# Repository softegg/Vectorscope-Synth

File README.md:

# Music Synthesizer for the Hackaday Supercon 2024/ Europe 2024 Vectorscope Badge

This is an add on for the Hackaday Superconference 2023 / Hackaday Europe(Berlin) 2024 Vectorscope badge that adds a small virtual analog synthesizer based on the [Stylish Trucker Belt Synthesizer](https://github.com/softegg/Stylish-Trucker-Belt-Synthesizer).

It should work with all of the source code from that, so for now get it there.
This has not yet been tested, so if you want to build one, be aware that it might be broken. In particular, I'm worried that the two batteries in the badge might not have the oomph to drive the vectorscope with the RPI 2040 and screen as well as the synth's Bluepill STM32, LED ring, and amplifier.

This might need additional battery or USB power support.

The design is very much in flux as we have very limited time before the show, and the modules used in the end product are going to be limited by what we can get delivered quickly in Berlin, as two week+ lead times for AliExpress parts are just not doable!
This is intended for a workshop, but we've been reluctant to commit before we are sure that it will work and that we can get the parts.

So, you might be able to do a $20 workshop and get one, or you might have to go find parts and build your own. It might work, or it might be crap.

There is so much we don't know.

I hope you can enjoy it, at least!!

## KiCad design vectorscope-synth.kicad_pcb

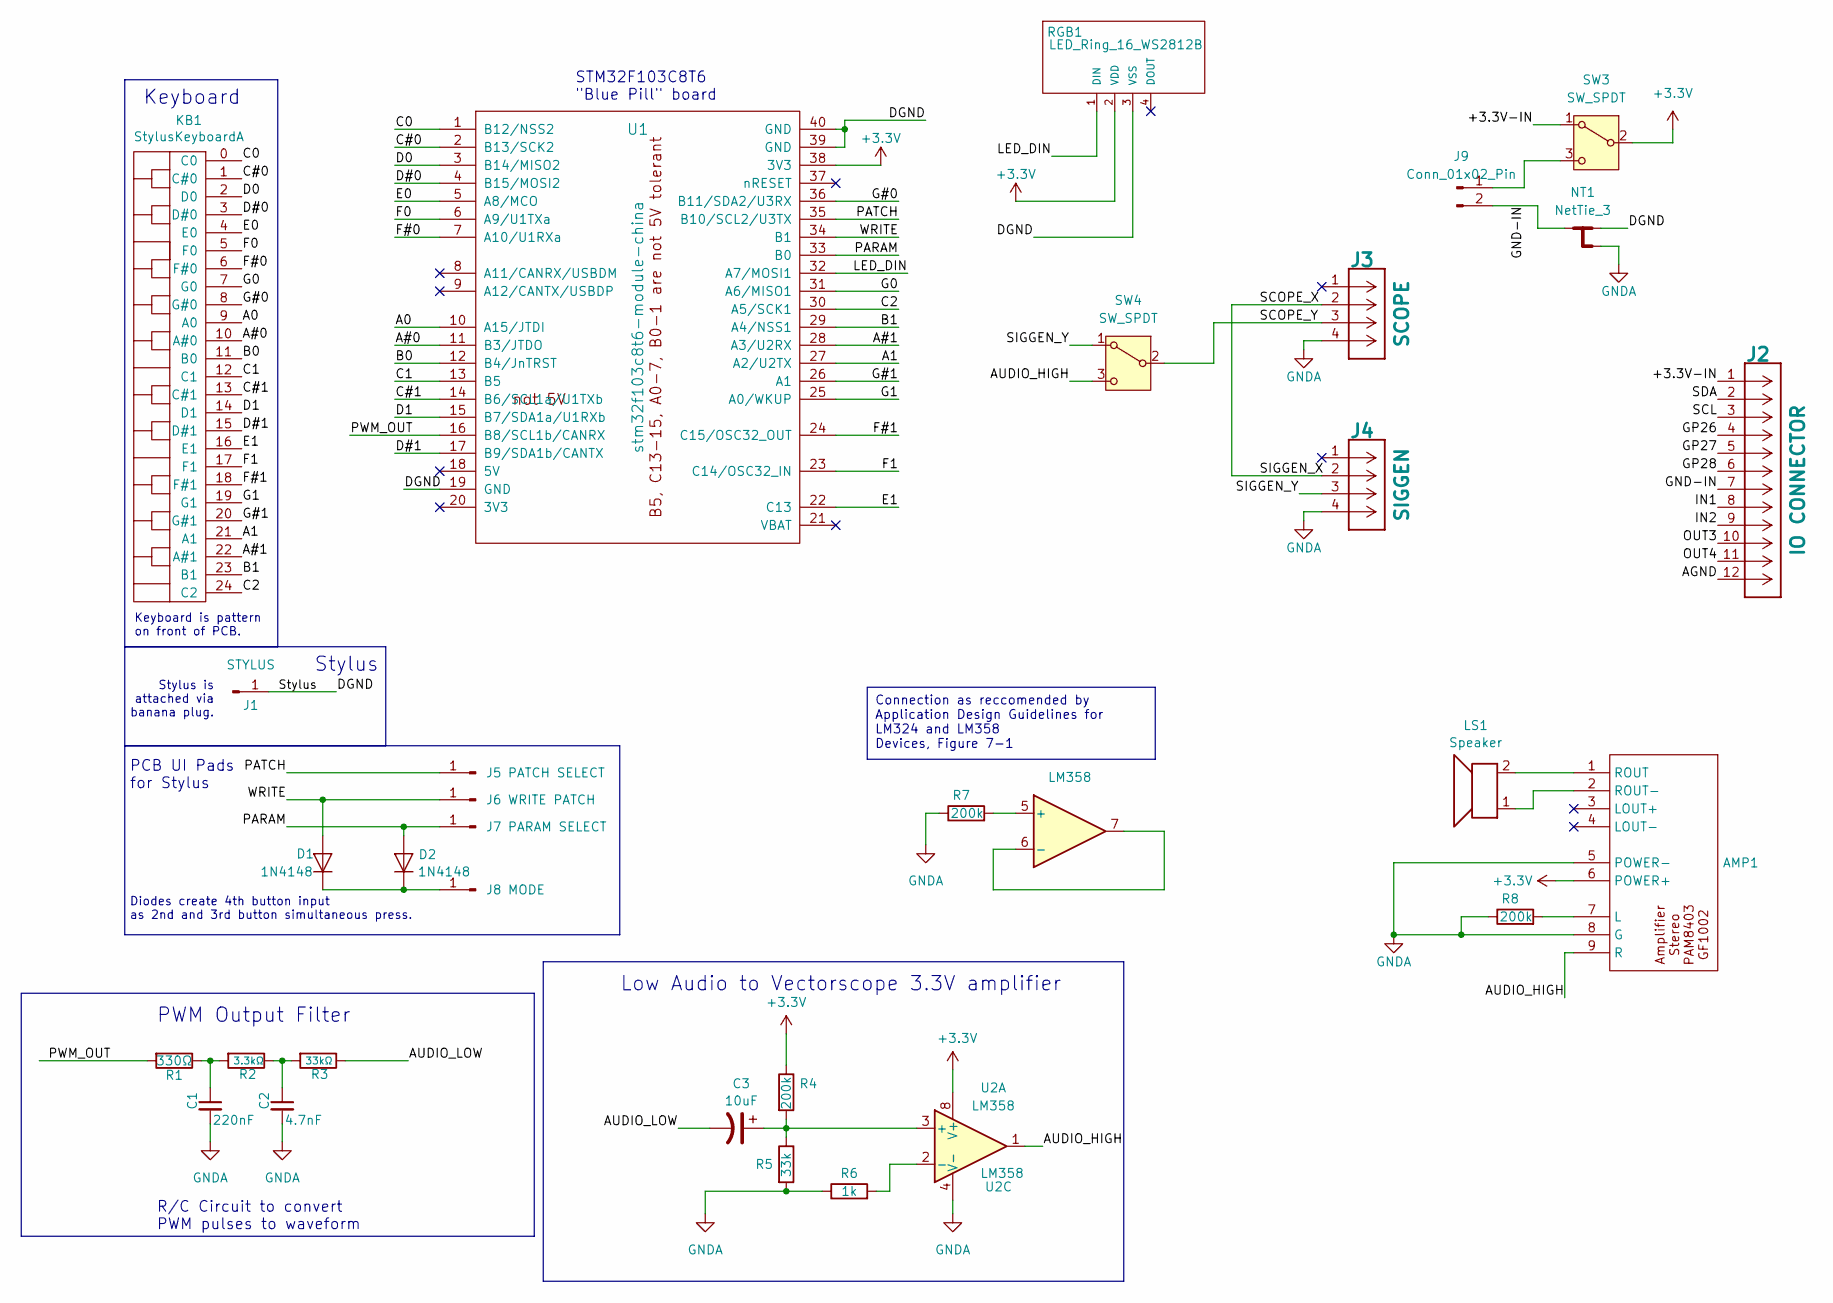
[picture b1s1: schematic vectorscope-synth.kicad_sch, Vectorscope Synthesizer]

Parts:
AMP1: GF1002-PAM8403_Amplifier_Module
C1: 220nF; C_Disc_D5.0mm_W2.5mm_P5.00mm+SMD
C2: 4.7nF; C_Disc_D5.0mm_W2.5mm_P5.00mm+SMD
C3: 10uF; CP_Radial_D5.0mm_P2.50mm
D1, D2: 1N4148; D_DO-35_SOD27_P7.62mm_Horizontal+SMD
J1: STYLUS; SmallRoundTouchPad
J2: IO CONNECTOR; PinSocket_1x12_P2.54mm_Horizontal
J3: SCOPE; PinSocket_1x04_P2.54mm_Horizontal
J4: SIGGEN; PinSocket_1x04_P2.54mm_Horizontal
J5: PATCH SELECT; SmallRoundTouchPad
J6: WRITE PATCH; SmallRoundTouchPad
J7: PARAM SELECT; SmallRoundTouchPad
J8: MODE; SmallRoundTouchPad
J9: Conn_01x02_Pin; PinHeader_1x02_P2.54mm_Vertical
KB1: StylusKeyboardA; StylusKeyboard
LS1: Speaker; PinSocket_1x02_P2.54mm_Vertical
NT1: NetTie_3; NetTie-3_SMD_Pad0.5mm
R1: 330Ω; R_Axial_DIN0204_L3.6mm_D1.6mm_P3.81mm_Horizontal+SMD804
R2: 3.3kΩ; R_Axial_DIN0204_L3.6mm_D1.6mm_P3.81mm_Horizontal+SMD804
R3: 33kΩ; R_Axial_DIN0204_L3.6mm_D1.6mm_P3.81mm_Horizontal+SMD804
R4: 200k; R_Axial_DIN0204_L3.6mm_D1.6mm_P5mm_Horizontal+SMD804
R5: 33k; R_Axial_DIN0204_L3.6mm_D1.6mm_P5mm_Horizontal+SMD804
R6: 1k; R_Axial_DIN0204_L3.6mm_D1.6mm_P5mm_Horizontal+SMD804
R7, R8: 200k; R_Axial_DIN0204_L3.6mm_D1.6mm_P7.62mm_Horizontal+SMD804
RGB1: LED_Ring_16_WS2812B; LED RING 16 WS2812B
SW3, SW4: SW_SPDT; PinHeader_1x03_P2.54mm_Vertical
U1: stm32f103c8t6-module-china; stm32f103c8t6-module-china-smd
U2: LM358; DIP-8_W7.62mm_LongPads

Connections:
+3.3V: AMP1.6 (POWER+), R4.1, RGB1.2 (VDD), SW3.2 (B), U1.38 (3V3), U2.8 (V+)
/+3.3V-IN: J2.1, SW3.1 (A)
/A0: KB1.9 (A0), U1.10 (A15/JTDI)
/A1: KB1.21 (A1), U1.27 (A2/U2TX)
/A#0: KB1.10 (A#0), U1.11 (B3/JTDO)
/A#1: KB1.22 (A#1), U1.28 (A3/U2RX)
/AGND: J2.12
/AUDIO_HIGH: AMP1.9 (R), SW4.3 (C), U2.1
/AUDIO_LOW: C3.2, R3.1
/B0: KB1.11 (B0), U1.12 (B4/JnTRST)
/B1: KB1.23 (B1), U1.29 (A4/NSS1)
/C0: KB1.0 (C0), U1.1 (B12/NSS2)
/C1: KB1.12 (C1), U1.13 (B5)
/C2: KB1.24 (C2), U1.30 (A5/SCK1)
/C#0: KB1.1 (C#0), U1.2 (B13/SCK2)
/C#1: KB1.13 (C#1), U1.14 (B6/SCL1a/U1TXb)
/D0: KB1.2 (D0), U1.3 (B14/MISO2)
/D1: KB1.14 (D1), U1.15 (B7/SDA1a/U1RXb)
/D#0: KB1.3 (D#0), U1.4 (B15/MOSI2)
/D#1: KB1.15 (D#1), U1.17 (B9/SDA1b/CANTX)
/DGND: J1.1, NT1.1, RGB1.3 (VSS), U1.19 (GND), U1.39 (GND), U1.40 (GND)
/E0: KB1.4 (E0), U1.5 (A8/MCO)
/E1: KB1.16 (E1), U1.22 (C13)
/F0: KB1.5 (F0), U1.6 (A9/U1TXa)
/F1: KB1.17 (F1), U1.23 (C14/OSC32_IN)
/F#0: KB1.6 (F#0), U1.7 (A10/U1RXa)
/F#1: KB1.18 (F#1), U1.24 (C15/OSC32_OUT)
/G0: KB1.7 (G0), U1.31 (A6/MISO1)
/G1: KB1.19 (G1), U1.25 (A0/WKUP)
/G#0: KB1.8 (G#0), U1.36 (B11/SDA2/U3RX)
/G#1: KB1.20 (G#1), U1.26 (A1)
/GND-IN: J2.7, J9.2, NT1.2
/GP26: J2.4; also elsewhere on the board
/GP27: J2.5; also elsewhere on the board
/GP28: J2.6; also elsewhere on the board
/IN1: J2.8; also elsewhere on the board
/IN2: J2.9; also elsewhere on the board
/LED_DIN: RGB1.1 (DIN), U1.32 (A7/MOSI1)
/OUT3: J2.10; also elsewhere on the board
/OUT4: J2.11; also elsewhere on the board
/PARAM: D2.2 (A), J7.1, U1.33 (B0)
/PATCH: J5.1, U1.35 (B10/SCL2/U3TX)
/PWM_OUT: R1.2, U1.16 (B8/SCL1b/CANRX)
/SCL: J2.3; also elsewhere on the board
/SCOPE_X: J3.2, J4.2
/SCOPE_Y: J3.3, SW4.2 (B)
/SDA: J2.2; also elsewhere on the board
/SIGGEN_Y: J4.3, SW4.1 (A)
/WRITE: D1.2 (A), J6.1, U1.34 (B1)
GNDA: AMP1.5 (POWER-), AMP1.8 (G), C1.2, C2.2, J3.4, J4.4, NT1.3, R5.2, R6.1, R7.1, R8.1, U2.4 (V-); also elsewhere on the board
unnamed: AMP1.7 (L), R8.2
unnamed: AMP1.1 (ROUT), LS1.2
unnamed: AMP1.2 (ROUT-), LS1.1
unnamed: C1.1, R1.1, R2.2
unnamed: C2.1, R2.1, R3.2
unnamed: D1.1 (K), D2.1 (K), J8.1
unnamed: J9.1, SW3.3 (C)
unnamed: C3.1, R4.2, R5.1, U2.3 (+)
unnamed: R6.2, U2.2 (-)
unnamed: R7.2, U2.5 (+)
unnamed: U2.6 (-), U2.7

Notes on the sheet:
Connection as reccomended by Application Design Guidelines for LM324 and LM358 Devices, Figure 7-1
Stylus
PWM Output Filter
STM32F103C8T6 "Blue Pill" board
R/C Circuit to convert PWM pulses to waveform
Keyboard is pattern on front of PCB.
PCB UI Pads for Stylus
Keyboard
Low Audio to Vectorscope 3.3V amplifier
Stylus is attached via banana plug.
Diodes create 4th button input as 2nd and 3rd button simultaneous press.

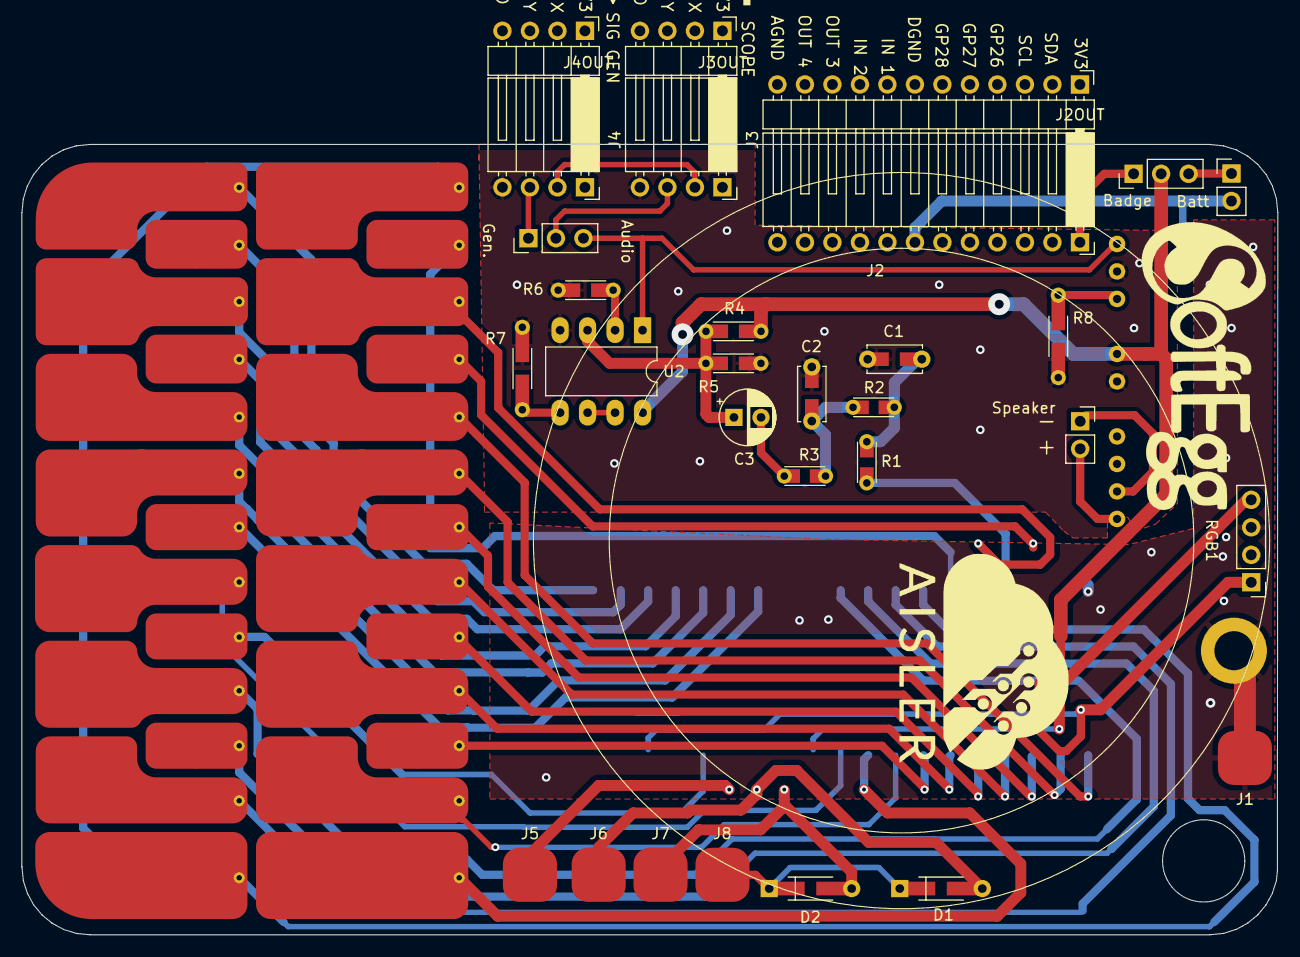
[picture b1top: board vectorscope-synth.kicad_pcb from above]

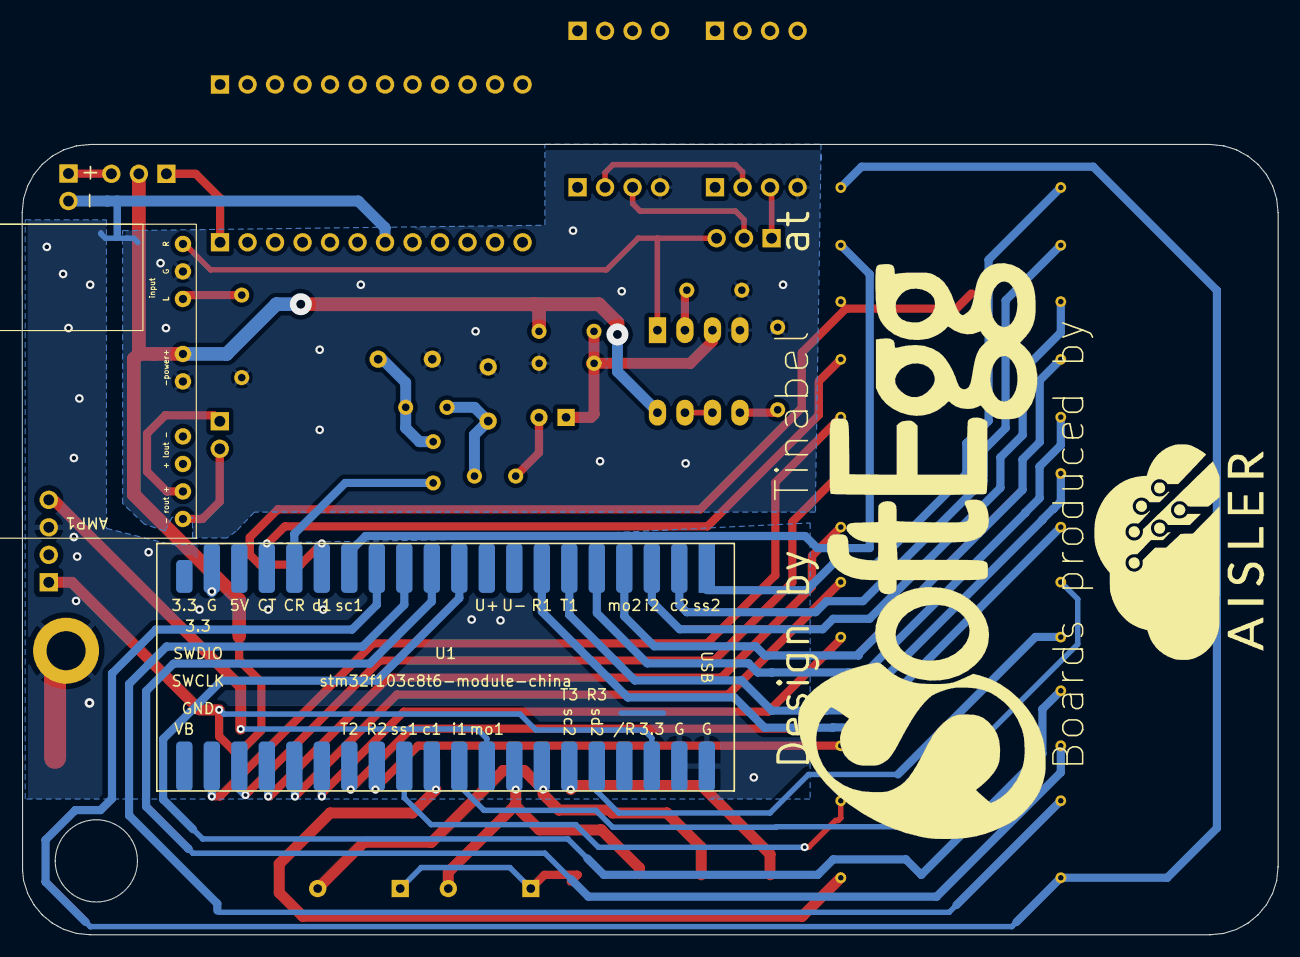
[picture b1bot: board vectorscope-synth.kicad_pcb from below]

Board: 2 copper layers, 116.0 x 73.0 mm, 34 parts (3 on the bottom side), 60 nets.

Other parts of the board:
J2OUT: IO CONNECTOR; PinHeader_1x12_P2.54mm_Horizontal
J3OUT: SCOPE; PinHeader_1x04_P2.54mm_Horizontal
J4OUT: SIGGEN; PinHeader_1x04_P2.54mm_Horizontal

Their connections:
/GP26: J2OUT.4; also elsewhere on the board
/GP27: J2OUT.5; also elsewhere on the board
/GP28: J2OUT.6; also elsewhere on the board
/IN1: J2OUT.8; also elsewhere on the board
/IN2: J2OUT.9; also elsewhere on the board
/OUT3: J2OUT.10; also elsewhere on the board
/OUT4: J2OUT.11; also elsewhere on the board
/SCL: J2OUT.3; also elsewhere on the board
/SDA: J2OUT.2; also elsewhere on the board
GNDA: J3OUT.4, J4OUT.4; also elsewhere on the board

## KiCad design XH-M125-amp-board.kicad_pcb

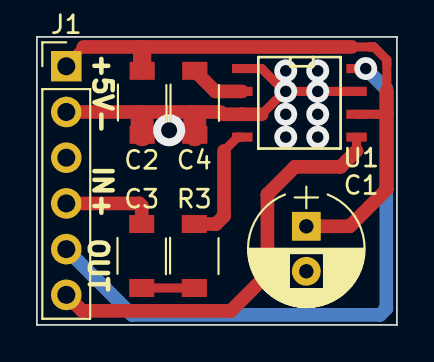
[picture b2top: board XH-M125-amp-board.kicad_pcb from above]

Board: 2 copper layers, 20.0 x 16.0 mm, 7 parts (0 on the bottom side), 8 nets.

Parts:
C1: 470uF; CP_Radial_D6.3mm_P2.50mm
C2, C4: 1uF; C_1509
C3: 0.39uF; C_1509
J1: Conn_01x06; Pin_Header_Straight_1x06_Pitch2.54mm
R3: R; C_1509
U1: XPT8871; SOIC-8-N

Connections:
/GND: C1.2, C2.2, C4.2, J1.2, J1.3, U1.1, U1.3, U1.7
/VCC: C1.1, C2.1, J1.1, U1.6
/VIN: C3.2, J1.4
/VO1: J1.6, U1.5
/VO2: J1.5, U1.8
unnamed: C3.1, R3.2
unnamed: C4.1, U1.2
unnamed: R3.1, U1.4

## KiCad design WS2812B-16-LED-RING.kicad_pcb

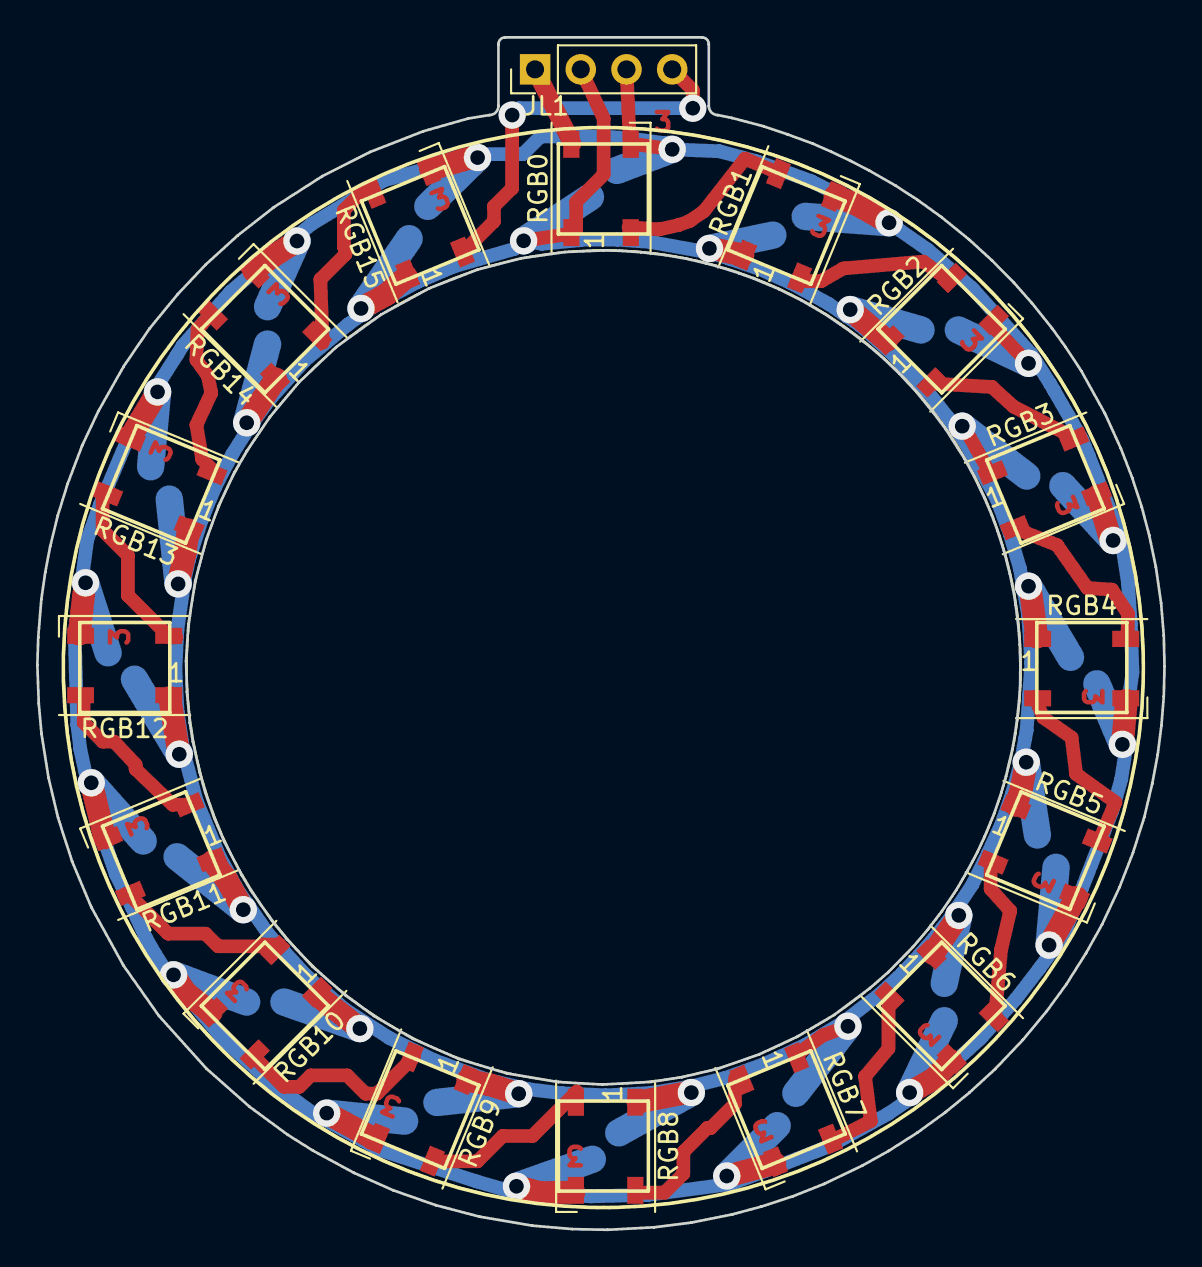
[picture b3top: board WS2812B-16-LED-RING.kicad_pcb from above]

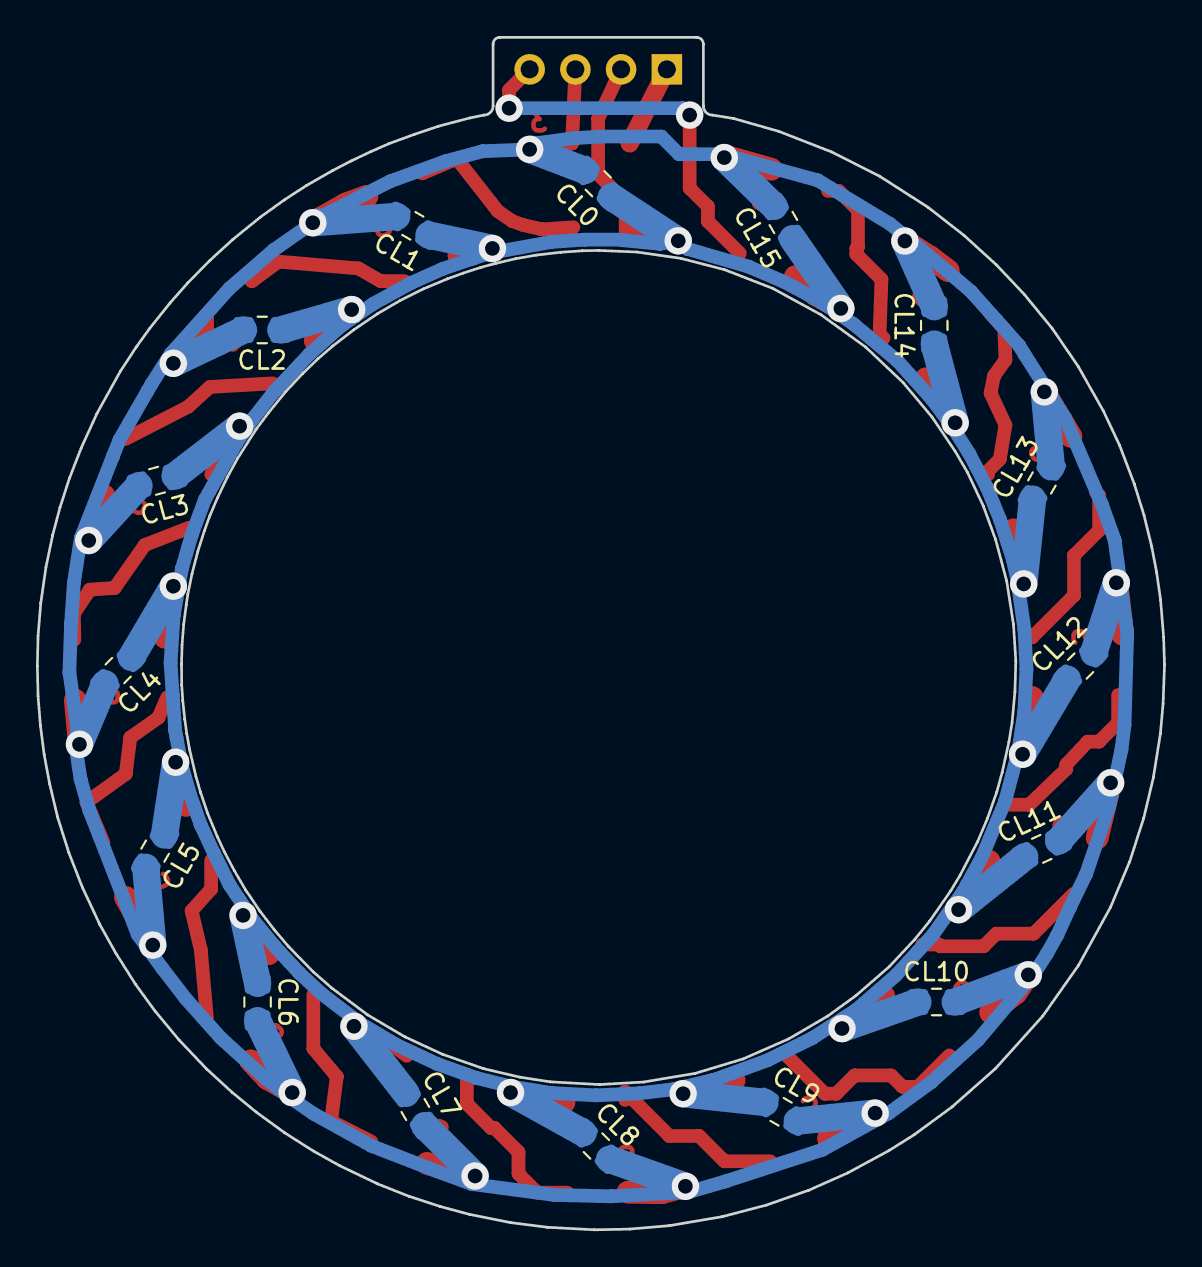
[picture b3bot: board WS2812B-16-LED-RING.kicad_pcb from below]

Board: 2 copper layers, 62.6 x 66.2 mm, 33 parts (16 on the bottom side), 19 nets.

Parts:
CL0, CL1, CL2, CL3, CL4, CL5, CL6, CL7, CL8, CL9, CL10, CL11, CL12, CL13, CL14, CL15: 104; C_0805_2012Metric_Pad1.18x1.45mm_HandSolder
JL1: Pin_Header_Straight_1x04_Pitch2.54mm
RGB0, RGB1, RGB2, RGB3, RGB4, RGB5, RGB6, RGB7, RGB8, RGB9, RGB10, RGB11, RGB12, RGB13, RGB14, RGB15: WS2812B; LED_WS2812B_PLCC4_5.0x5.0mm_P3.2mm

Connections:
/DIN: JL1.1, RGB0.4 (DIN)
/DOUT: JL1.4, RGB15.2 (DOUT)
/VIN: CL0.1, CL1.1, CL2.1, CL3.1, CL4.1, CL5.1, CL6.1, CL7.1, CL8.1, CL9.1, CL10.1, CL11.1, CL12.1, CL13.1, CL14.1, CL15.1, JL1.2, RGB0.1 (VDD), RGB1.1 (VDD), RGB2.1 (VDD), RGB3.1 (VDD), RGB4.1 (VDD), RGB5.1 (VDD), RGB6.1 (VDD), RGB7.1 (VDD), RGB8.1 (VDD), RGB9.1 (VDD), RGB10.1 (VDD), RGB11.1 (VDD), RGB12.1 (VDD), RGB13.1 (VDD), RGB14.1 (VDD), RGB15.1 (VDD)
GND: CL0.2, CL1.2, CL2.2, CL3.2, CL4.2, CL5.2, CL6.2, CL7.2, CL8.2, CL9.2, CL10.2, CL11.2, CL12.2, CL13.2, CL14.2, CL15.2, JL1.3, RGB0.3 (VSS), RGB1.3 (VSS), RGB2.3 (VSS), RGB3.3 (VSS), RGB4.3 (VSS), RGB5.3 (VSS), RGB6.3 (VSS), RGB7.3 (VSS), RGB8.3 (VSS), RGB9.3 (VSS), RGB10.3 (VSS), RGB11.3 (VSS), RGB12.3 (VSS), RGB13.3 (VSS), RGB14.3 (VSS), RGB15.3 (VSS)
unnamed: RGB0.2 (DOUT), RGB1.4 (DIN)
unnamed: RGB1.2 (DOUT), RGB2.4 (DIN)
unnamed: RGB2.2 (DOUT), RGB3.4 (DIN)
unnamed: RGB3.2 (DOUT), RGB4.4 (DIN)
unnamed: RGB4.2 (DOUT), RGB5.4 (DIN)
unnamed: RGB5.2 (DOUT), RGB6.4 (DIN)
unnamed: RGB6.2 (DOUT), RGB7.4 (DIN)
unnamed: RGB7.2 (DOUT), RGB8.4 (DIN)
unnamed: RGB8.2 (DOUT), RGB9.4 (DIN)
unnamed: RGB9.2 (DOUT), RGB10.4 (DIN)
unnamed: RGB10.2 (DOUT), RGB11.4 (DIN)
unnamed: RGB11.2 (DOUT), RGB12.4 (DIN)
unnamed: RGB12.2 (DOUT), RGB13.4 (DIN)
unnamed: RGB13.2 (DOUT), RGB14.4 (DIN)
unnamed: RGB14.2 (DOUT), RGB15.4 (DIN)

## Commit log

2024-04-03 Vectorscope Synth KiCAD version 0.1 complete Uses Bluepill STM32F103C8T6 microcontroller A generic WS2812B 16 LED Ring An XH-M125 XPT8871 Amplifier Board and a handful of passives for a low pass filt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
2024-04-03 Credits, and schematic PDF
2024-04-07 Added op amp LM358 circuit to move PWM levels to vectorscope 0-3.3v. Replaced XH-M125/XPT8871 amp with GF1002/PAM8403 stereo amp with volume control. Enlarged many traces. Added logos for SoftEgg and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
2024-04-07 Update README.md
    Changed pictures to pictures stored in the "Docs" directory.
2024-04-11 PCB and Schematic updates by Thea @ Aisler
2024-04-11 Note: This is NOT the version used in the Hackaday Europe 2024 Workshop, that is the previous version. This is a version that fixes the LED ring wiring problem with that one, and has a footprint that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
2024-04-11 Changed Resstor to give good values for the vector scope. Updated headers to give proper credits.
2024-04-27 Enlarged holes for amplifier PCB mounting. Updated PCB pics and Schematic PDF to match revisions.
2024-04-27 Was there a change that was not checked in?
2025-02-02 propsed solution to amp problem
2025-02-24 correct patch resistor values for updated measurements
